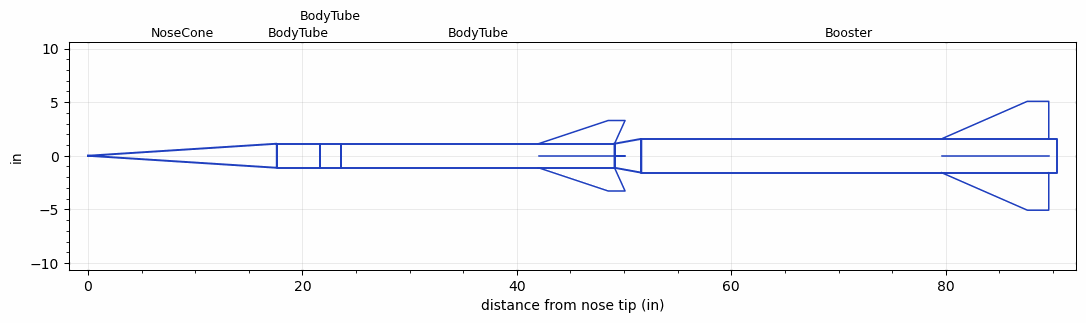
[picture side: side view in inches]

<RASAeroDocument>
 <FileVersion>2</FileVersion>
 <RocketDesign>
  <NoseCone>
   <Length>17.6063</Length>
   <Diameter>2.2441</Diameter>
   <Shape>Conical</Shape>
   <Location>0</Location>
  </NoseCone>
  <BodyTube>
   <Length>4</Length>
   <Diameter>2.2441</Diameter>
   <Location>17.6063</Location>
  </BodyTube>
  <BodyTube>
   <Length>2</Length>
   <Diameter>2.2441</Diameter>
   <Location>21.6063</Location>
  </BodyTube>
  <BodyTube>
   <Length>25.4999</Length>
   <Diameter>2.2441</Diameter>
   <Location>23.6063</Location>
   <Fin>
    <Count>4</Count>
    <Chord>7.0866</Chord>
    <Span>2.1653</Span>
    <SweepDistance>6.4961</SweepDistance>
    <TipChord>1.5748</TipChord>
    <Thickness>0.1181</Thickness>
    <LERadius>0.05</LERadius>
    <Location>7.0866</Location>
    <AirfoilSection>Hexagonal</AirfoilSection>
    <FX1>0.25</FX1>
    <FX3>0.25</FX3>
   </Fin>
  </BodyTube>
  <Booster>
   <Length>38.7499</Length>
   <Diameter>3.1496</Diameter>
   <InsideDiameter>2.2441</InsideDiameter>
   <Location>49.1062</Location>
   <ShoulderLength>2.5</ShoulderLength>
   <Fin>
    <Count>4</Count>
    <Chord>10</Chord>
    <Span>3.5</Span>
    <SweepDistance>8</SweepDistance>
    <TipChord>2</TipChord>
    <Thickness>0.1181</Thickness>
    <LERadius>0.05</LERadius>
    <Location>10.75</Location>
    <AirfoilSection>Hexagonal</AirfoilSection>
    <FX1>0.25</FX1>
    <FX3>0.25</FX3>
   </Fin>
  </Booster>
  <Surface>Smooth Paint</Surface>
  <ModifiedBarrowman>True</ModifiedBarrowman>
  <Turbulence>False</Turbulence>
  <UseBooster1>True</UseBooster1>
  <UseBooster2>False</UseBooster2>
  <Comments>Dust bloom?
Cactus Devil?</Comments>
 </RocketDesign>
 <LaunchSite>
  <Altitude>1250</Altitude>
  <Pressure>24.98</Pressure>
  <RodAngle>0</RodAngle>
  <RodLength>14</RodLength>
  <Temperature>70</Temperature>
  <WindSpeed>15</WindSpeed>
 </LaunchSite>
 <Recovery>
  <Altitude1>1000</Altitude1>
  <Altitude2>0</Altitude2>
  <DeviceType1>Parachute</DeviceType1>
  <DeviceType2>None</DeviceType2>
  <Event1>True</Event1>
  <Event2>False</Event2>
  <Size1>47.9999</Size1>
  <Size2>0</Size2>
  <EventType1>Altitude</EventType1>
  <EventType2>None</EventType2>
  <CD1>0.8</CD1>
  <CD2>0</CD2>
 </Recovery>
 <SimulationList>
  <Simulation>
   <SustainerEngine>K1100T  (AT)</SustainerEngine>
   <SustainerLaunchWt>6</SustainerLaunchWt>
   <SustainerNozzleDiameter>1.25</SustainerNozzleDiameter>
   <SustainerCG>31.88</SustainerCG>
   <SustainerIgnitionDelay>1</SustainerIgnitionDelay>
   <Booster1Engine>L1150  (AT)</Booster1Engine>
   <Booster1LaunchWt>21</Booster1LaunchWt>
   <Booster1SeparationDelay>0</Booster1SeparationDelay>
   <Booster1IgnitionDelay>0</Booster1IgnitionDelay>
   <Booster1CG>59</Booster1CG>
   <Booster1NozzleDiameter>1.875</Booster1NozzleDiameter>
   <IncludeBooster1>True</IncludeBooster1>
   <Booster2Delay>0</Booster2Delay>
   <IncludeBooster2>False</IncludeBooster2>
   <TimetoApogee>41.3296</TimetoApogee>
   <MaxAltitude>34836.52</MaxAltitude>
   <MaxVelocity>2949.615</MaxVelocity>
  </Simulation>
 </SimulationList>
</RASAeroDocument>
